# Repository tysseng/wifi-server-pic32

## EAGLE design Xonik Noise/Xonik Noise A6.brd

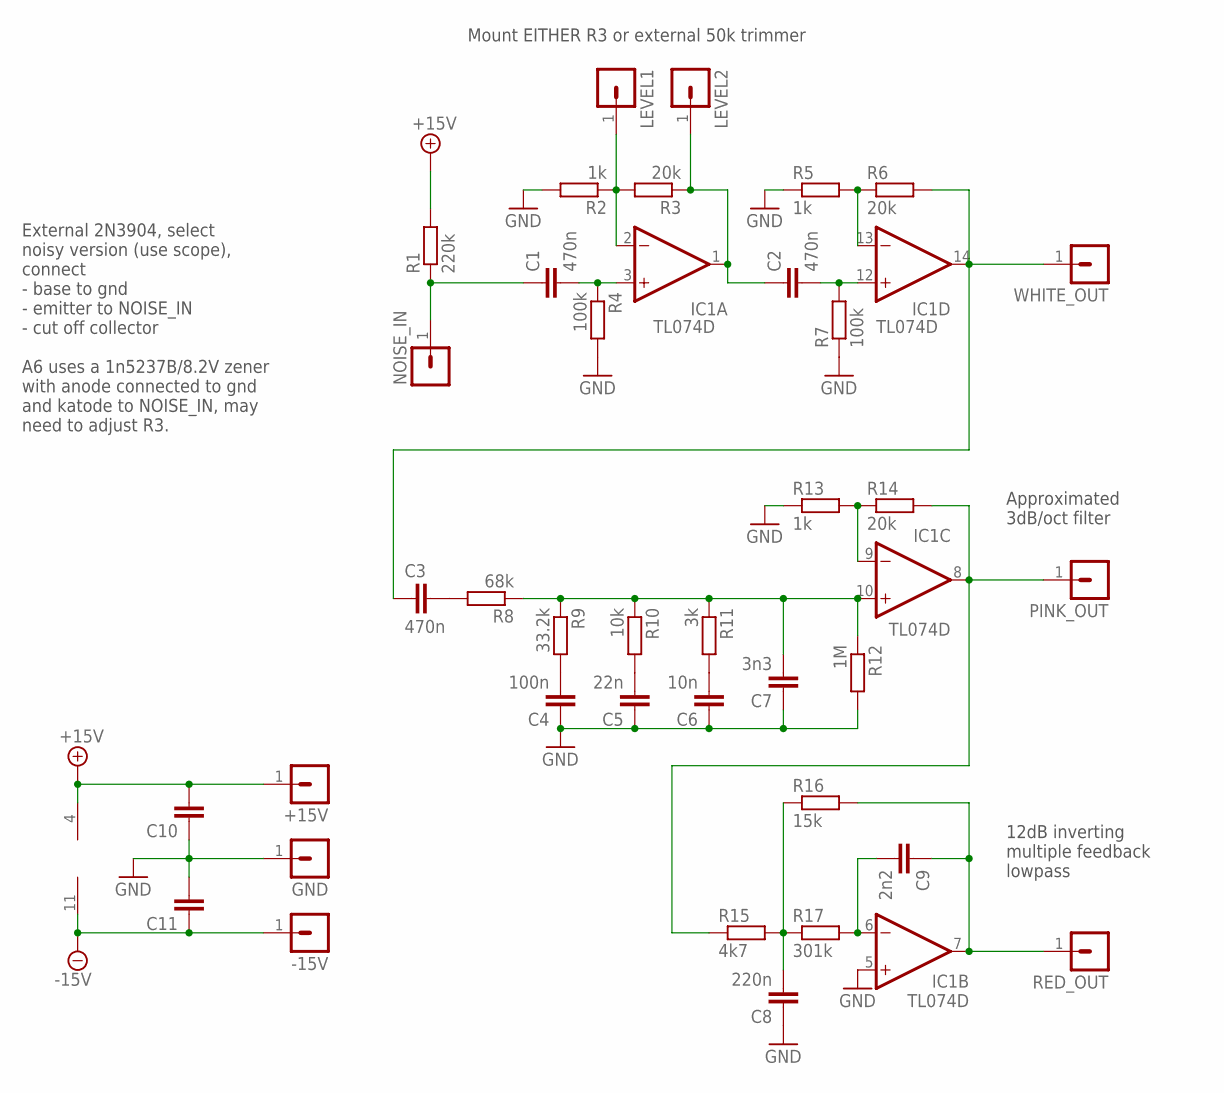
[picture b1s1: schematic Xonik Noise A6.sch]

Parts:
+15V: MA01-1JP; SIP-PIN01-1J
-15V: MA01-1JP; SIP-PIN01-1J
C1, C2, C3: 470n; C0805
C4: 100n; C0805
C5: 22n; C0805
C6: 10n; C0805
C7: 3n3; C0805
C8: 220n; C0805
C9: 2n2; C0805
C10, C11: C-EUC0603; C0603
GND: MA01-1JP; SIP-PIN01-1J
IC1: TL074D; SO14
LEVEL1, LEVEL2: MA01-1JP; SIP-PIN01-1J
NOISE_IN: MA01-1JP; SIP-PIN01-1J
PINK_OUT: MA01-1JP; SIP-PIN01-1J
R1: 220k; R0805
R2, R5, R13: 1k; R0805
R3, R6, R14: 20k; R0805
R4, R7: 100k; R0805
R8: 68k; R0805
R9: 33.2k; R0805
R10: 10k; R0805
R11: 3k; R0805
R12: 1M; R0805
R15: 4k7; R0805
R16: 15k; R0805
R17: 301k; R0805
RED_OUT: MA01-1JP; SIP-PIN01-1J
WHITE_OUT: MA01-1JP; SIP-PIN01-1J

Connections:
+15V: +15V.1, C10.2, IC1.4 (V+), R1.2
-15V: -15V.1, C11.1, IC1.11 (V-)
GND: C4.1, C5.1, C6.1, C7.1, C8.1, C10.1, C11.2, GND.1, IC1.5 (+IN), R2.2, R4.2, R5.1, R7.1, R12.2, R13.1
unnamed: IC1.2 (-IN), LEVEL1.1, R2.1, R3.2
unnamed: IC1.13 (-IN), R5.2, R6.1
unnamed: IC1.9 (-IN), R13.2, R14.1
unnamed: C4.2, R9.2
unnamed: C5.2, R10.2
unnamed: C6.2, R11.2
unnamed: C1.1, NOISE_IN.1, R1.1
unnamed: C1.2, IC1.3 (+IN), R4.1
unnamed: C2.1, IC1.1 (OUT), LEVEL2.1, R3.1
unnamed: C2.2, IC1.12 (+IN), R7.2
unnamed: C3.1, IC1.14 (OUT), R6.2, WHITE_OUT.1
unnamed: C7.2, IC1.10 (+IN), R8.1, R9.1, R10.1, R11.1, R12.1
unnamed: C3.2, R8.2
unnamed: IC1.8 (OUT), PINK_OUT.1, R14.2, R15.1
unnamed: C8.2, R15.2, R16.1, R17.1
unnamed: C9.2, IC1.6 (-IN), R17.2
unnamed: C9.1, IC1.7 (OUT), R16.2, RED_OUT.1

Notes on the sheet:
Mount EITHER R3 or external 50k trimmer
Approximated 3dB/oct filter
12dB inverting multiple feedback lowpass
External 2N3904, select noisy version (use scope), connect - base to gnd - emitter to NOISE_IN - cut off collector A6 uses a 1n5237B/8.2V zener with anode connected to gnd and katode to NOISE_IN, may need to adjust R3.

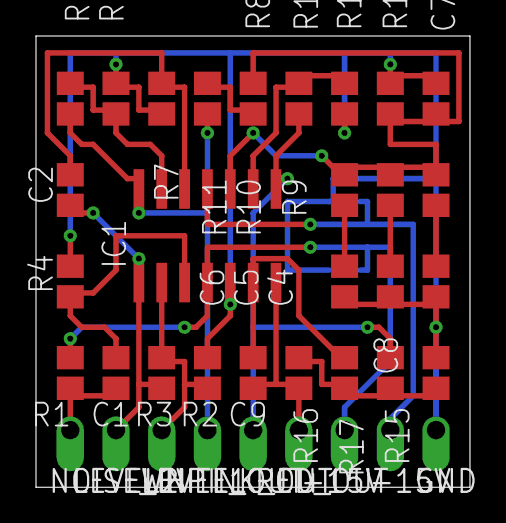
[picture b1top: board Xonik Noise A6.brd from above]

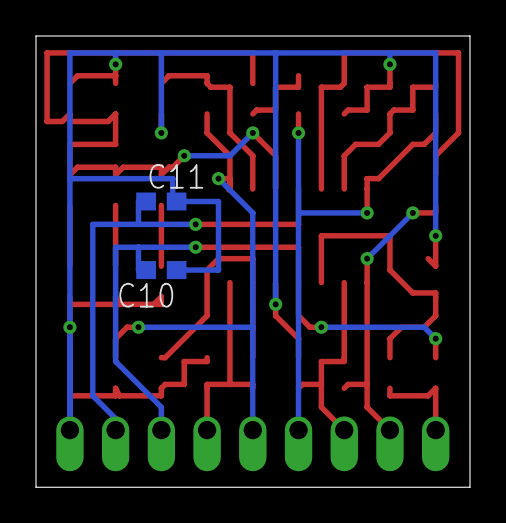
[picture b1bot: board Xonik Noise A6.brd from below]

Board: 2 copper layers, 24.1 x 25.1 mm, 38 parts (2 on the bottom side), 20 nets.

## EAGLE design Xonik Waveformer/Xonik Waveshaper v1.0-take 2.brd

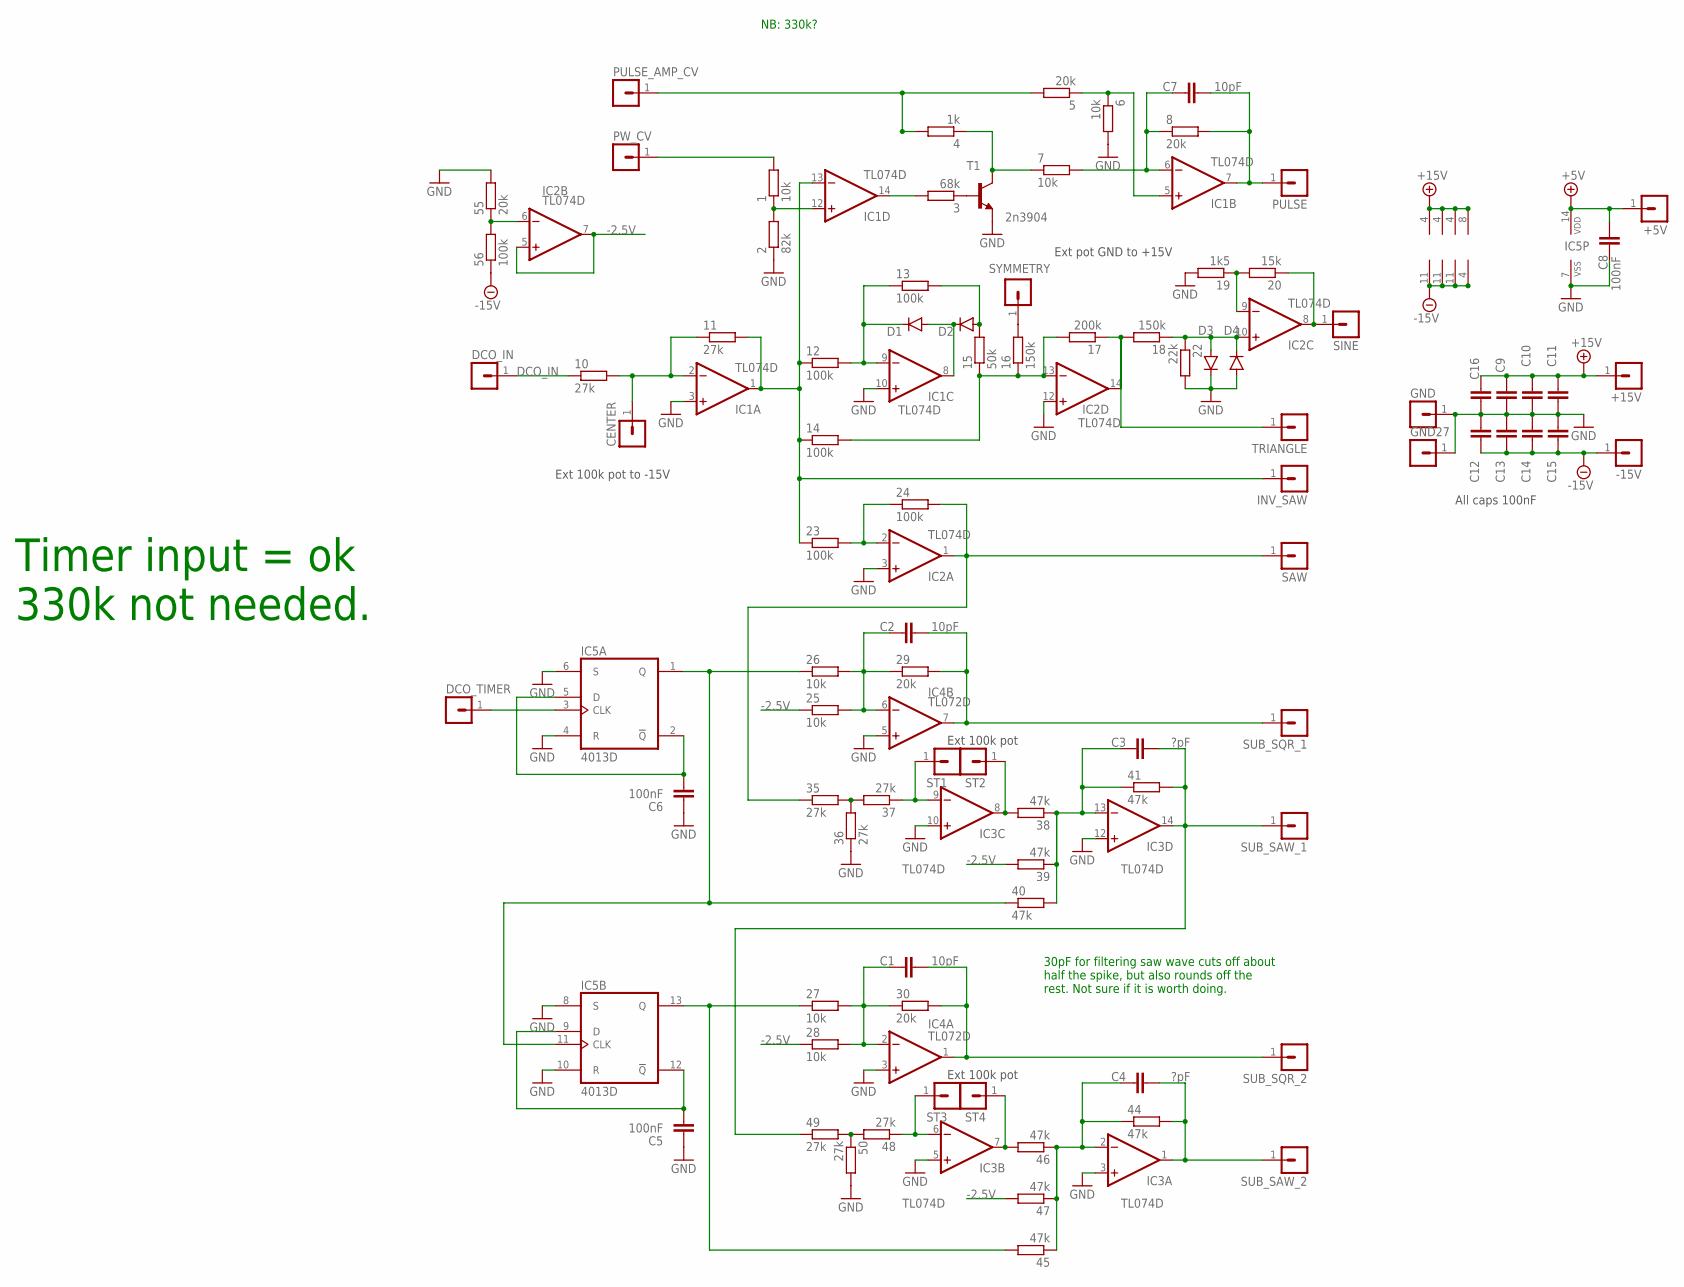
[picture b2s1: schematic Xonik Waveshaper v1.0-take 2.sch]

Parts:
1, 6, 7, 25, 26, 27, 28: 10k; R0805
2: 82k; R0805
3: 68k; R0805
4: 1k; R0805
5, 8, 29, 30, 55: 20k; R0805
10, 11, 35, 36, 37, 48, 49, 50: 27k; R0805
12, 13, 14, 23, 24, 56: 100k; R0805
15: 50k; R0805
16, 18: 150k; R0805
17: 200k; R0805
19: 1k5; R0805
20: 15k; R0805
22: 22k; R0805
38, 39, 40, 41, 44, 45, 46, 47: 47k; R0805
+5V, +15V: MA01-1JP; SIP-PIN01-1J
-15V: MA01-1JP; SIP-PIN01-1J
C1, C2, C7: 10pF; C0805
C3, C4: ?pF; C0805
C5, C6, C8: 100nF; C0805
C9, C10, C11, C12, C13, C14, C15, C16: 100nF; C0603K
CENTER: MA01-1JP; SIP-PIN01-1J
D1, D2, D3, D4: 1N41480805; D0805-J
DCO_IN: MA01-1JP; SIP-PIN01-1J
DCO_TIMER: MA01-1JP; SIP-PIN01-1J
GND, GND27: MA01-1JP; SIP-PIN01-1J
IC1, IC2, IC3: TL074D; SO14
IC4: TL072D; SO08J
IC5: 4013D; SO14J
INV_SAW: MA01-1JP; SIP-PIN01-1J
PULSE: MA01-1JP; SIP-PIN01-1J
PULSE_AMP_CV: MA01-1JP; SIP-PIN01-1J
PW_CV: MA01-1JP; SIP-PIN01-1J
SAW: MA01-1JP; SIP-PIN01-1J
SINE: MA01-1JP; SIP-PIN01-1J
ST1, ST2, ST3, ST4: MA01-1JP; SIP-PIN01-1J
SUB_SAW_1, SUB_SAW_2: MA01-1JP; SIP-PIN01-1J
SUB_SQR_1, SUB_SQR_2: MA01-1JP; SIP-PIN01-1J
SYMMETRY: MA01-1JP; SIP-PIN01-1J
T1: 2n3904; SOT23-BEC
TRIANGLE: MA01-1JP; SIP-PIN01-1J

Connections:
+5V: +5V.1, C8.2, IC5.14 (VDD)
+15V: +15V.1, C9.2, C10.2, C11.2, C16.2, IC1.4 (V+), IC2.4 (V+), IC3.4 (V+), IC4.8 (V+)
-2.5V: 25.1, 28.1, 39.2, 47.2, IC2.5 (+IN), IC2.7 (OUT)
-15V: 56.1, -15V.1, C12.1, C13.1, C14.1, C15.1, IC1.11 (V-), IC2.11 (V-), IC3.11 (V-), IC4.4 (V-)
AMP_CV: 4.2, 5.2, PULSE_AMP_CV.1
DCO_IN: 10.1, DCO_IN.1
GND: 2.1, 6.2, 19.2, 22.2, 36.1, 50.2, 55.2, C5.1, C6.1, C8.1, C9.1, C10.1, C11.1, C12.2, C13.2, C14.2, C15.2, C16.1, D3.C, D4.A, GND.1, GND27.1, IC1.3 (+IN), IC1.10 (+IN), IC2.3 (+IN), IC2.12 (+IN), IC3.3 (+IN), IC3.5 (+IN), IC3.10 (+IN), IC3.12 (+IN), IC4.3 (+IN), IC4.5 (+IN), IC5.4 (R), IC5.6 (S), IC5.7 (VSS), IC5.8 (S), IC5.10 (R), T1.E
unnamed: 1.1, 2.2, IC1.12 (+IN)
unnamed: 3.2, IC1.14 (OUT)
unnamed: 3.1, T1.B
unnamed: 4.1, 7.1, T1.C
unnamed: 5.1, 6.1, IC1.5 (+IN)
unnamed: 7.2, 8.1, C7.1, IC1.6 (-IN)
unnamed: 8.2, C7.2, IC1.7 (OUT), PULSE.1
unnamed: 11.2, 12.1, 14.1, 23.1, IC1.1 (OUT), IC1.13 (-IN), INV_SAW.1
unnamed: 10.2, 11.1, CENTER.1, IC1.2 (-IN)
unnamed: 12.2, 13.1, D1.C, IC1.9 (-IN)
unnamed: D1.A, D2.C, IC1.8 (OUT)
unnamed: 13.2, 15.2, D2.A
unnamed: 14.2, 15.1, 16.1, 17.2, IC2.13 (-IN)
unnamed: 23.2, 24.1, IC2.2 (-IN)
unnamed: 24.2, 35.1, IC2.1 (OUT), SAW.1
unnamed: 29.2, C2.2, IC4.7 (OUT), SUB_SQR_1.1
unnamed: 30.2, C1.2, IC4.1 (OUT), SUB_SQR_2.1
unnamed: 25.2, 26.2, 29.1, C2.1, IC4.6 (-IN)
unnamed: 46.2, IC3.7 (OUT), ST4.1
unnamed: 48.2, 49.2, 50.1
unnamed: 27.2, 28.2, 30.1, C1.1, IC4.2 (-IN)
unnamed: 35.2, 36.2, 37.2
unnamed: 37.1, IC3.9 (-IN), ST1.1
unnamed: 38.1, 39.1, 40.2, 41.1, C3.1, IC3.13 (-IN)
unnamed: 41.2, 49.1, C3.2, IC3.14 (OUT), SUB_SAW_1.1
unnamed: 48.1, IC3.6 (-IN), ST3.1
unnamed: 44.1, 45.1, 46.1, 47.1, C4.1, IC3.2 (-IN)
unnamed: 44.2, C4.2, IC3.1 (OUT), SUB_SAW_2.1
unnamed: C6.2, IC5.2 (!Q), IC5.5 (D)
unnamed: 26.1, 40.1, IC5.1 (Q), IC5.11 (CLK)
unnamed: 55.1, 56.2, IC2.6 (-IN)
unnamed: C5.2, IC5.9 (D), IC5.12 (!Q)
unnamed: 27.1, 45.2, IC5.13 (Q)
unnamed: 19.1, 20.2, IC2.9 (-IN)
unnamed: 16.2, SYMMETRY.1
unnamed: 17.1, 18.2, IC2.14 (OUT), TRIANGLE.1
unnamed: 18.1, 22.1, D3.A, D4.C, IC2.10 (+IN)
unnamed: 20.1, IC2.8 (OUT), SINE.1
unnamed: 38.2, IC3.8 (OUT), ST2.1
PW_CV: 1.2, PW_CV.1
SQR: DCO_TIMER.1, IC5.3 (CLK)

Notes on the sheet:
NB: 330k?
All caps 100nF
Ext 100k pot to -15V
Ext pot GND to +15V
Ext 100k pot
Timer input = ok 330k not needed.
30pF for filtering saw wave cuts off about half the spike, but also rounds off the rest. Not sure if it is worth doing.

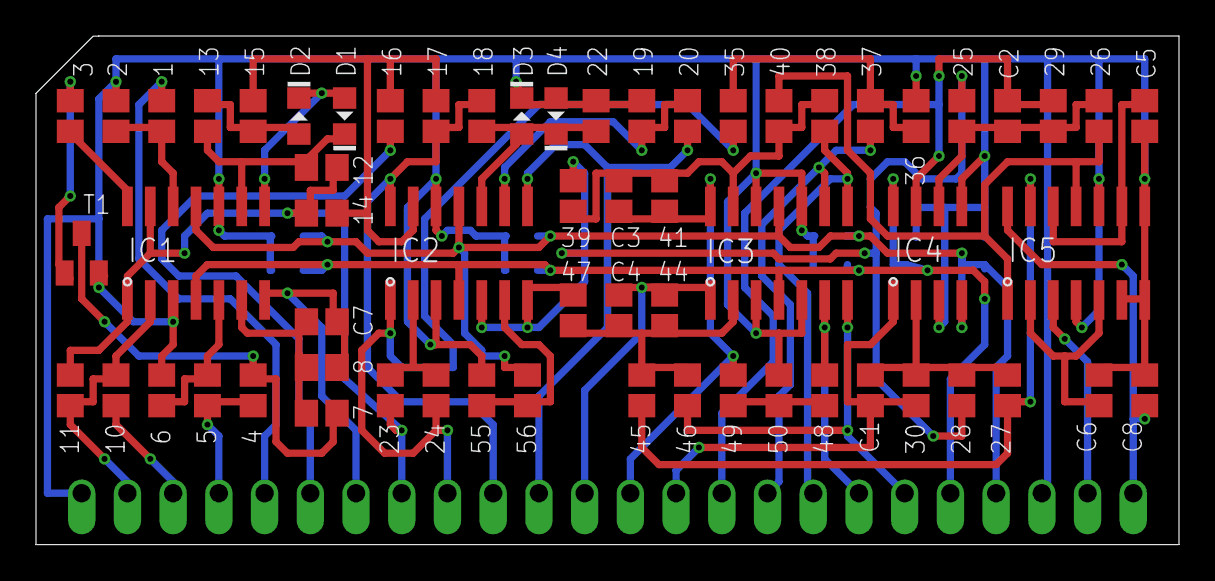
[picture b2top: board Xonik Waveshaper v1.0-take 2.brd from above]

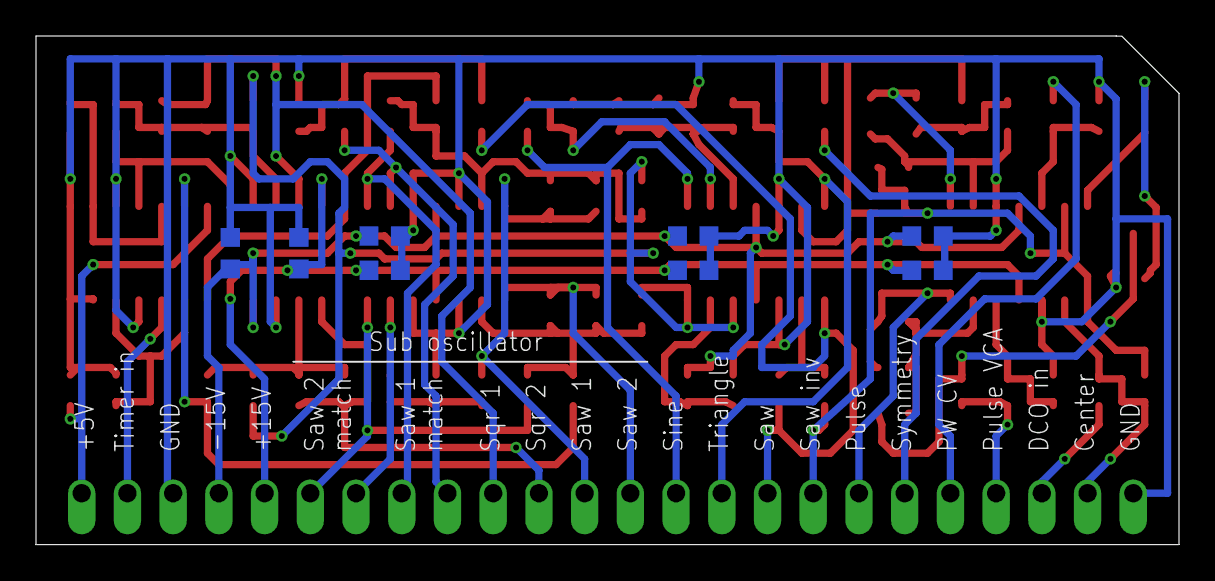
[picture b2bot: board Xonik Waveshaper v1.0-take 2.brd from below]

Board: 2 copper layers, 63.5 x 28.3 mm, 94 parts (8 on the bottom side), 48 nets.

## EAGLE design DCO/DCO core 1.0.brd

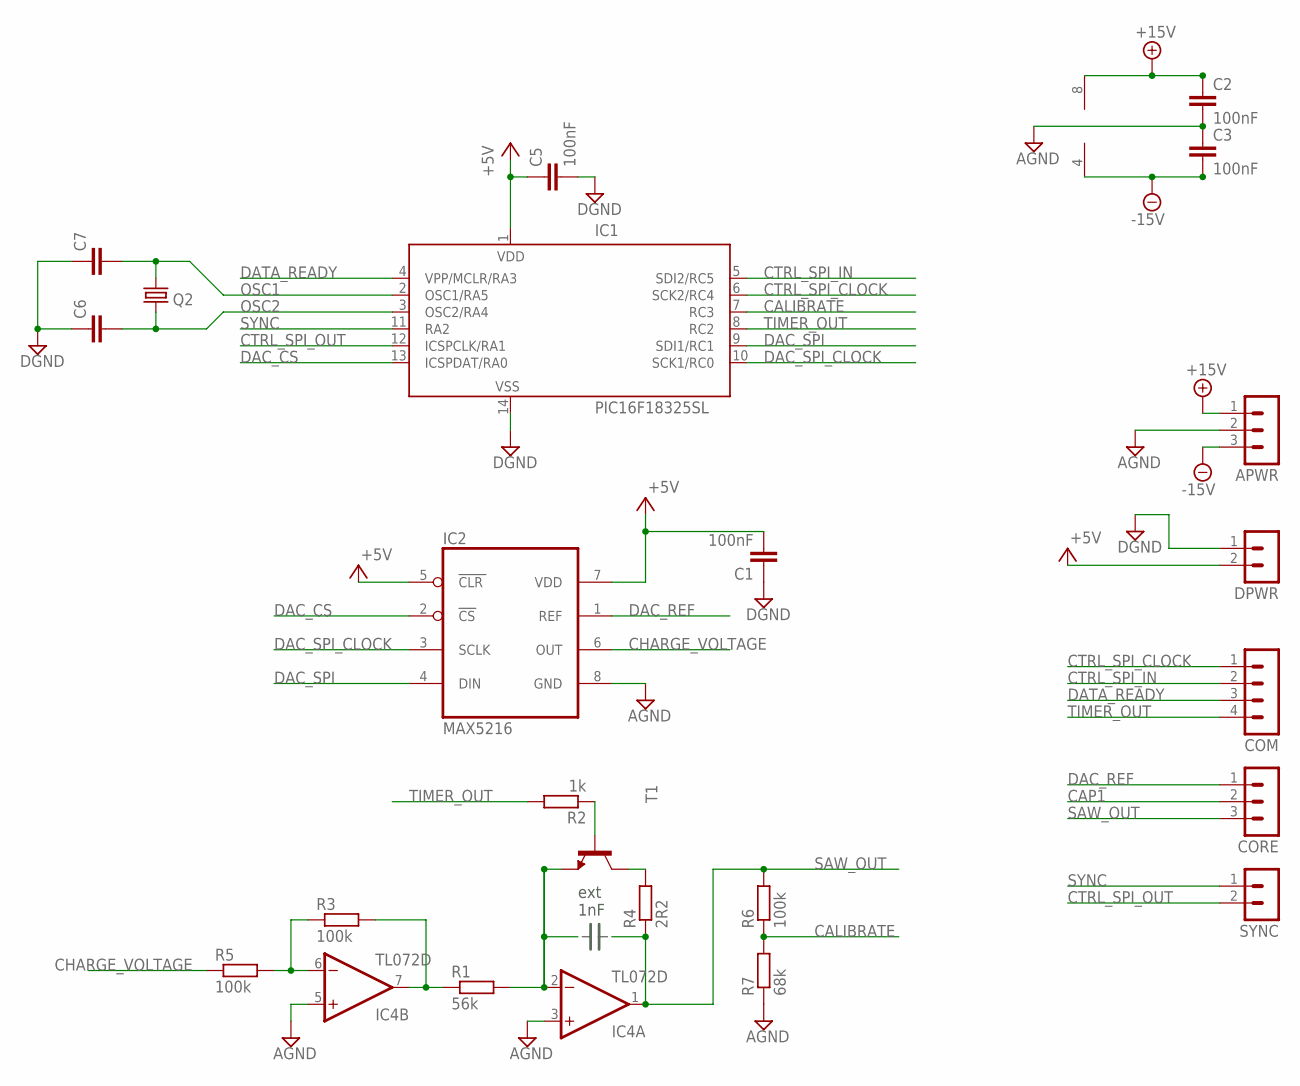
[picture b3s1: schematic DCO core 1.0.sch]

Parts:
APWR: MA03-1JP; SIP-PIN03-1J
C1, C2, C3, C5: 100nF; C0805
C6, C7: C-EUC0805; C0805
COM: MA04-1JP; SIP-PIN04-1J
CORE: MA03-1JP; SIP-PIN03-1J
DPWR: MA02-1JP; SIP-PIN02-1J
IC1: PIC16F18325SL; SO14J
IC2: MAX5216; UMAX8J
IC4: TL072D; SO08J
Q2: CRYSTALHC49S; HC49/S
R1: 56k; R0805
R2: 1k; R0805
R3, R5, R6: 100k; R0805
R4: 2R2; R0805
R7: 68k; R0805
SYNC: MA02-1JP; SIP-PIN02-1J
T1: MMBT3904LT1-NPN-SOT23-BEC; SOT23-BEC

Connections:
+5V: C1.2, C5.1, DPWR.2, IC1.1 (VDD), IC2.5 (CLR), IC2.7 (VDD)
+15V: APWR.1, C2.1, IC4.8 (V+)
-15V: APWR.3, C3.2, IC4.4 (V-)
AGND: APWR.2, C2.2, C3.1, IC2.8 (GND), IC4.3 (+IN), IC4.5 (+IN), R7.1
CALIBRATE: IC1.7 (RC3), R6.1, R7.2
CAP1: CORE.2, IC4.2 (-IN), R1.2, T1.E
CHARGE_VOLTAGE: IC2.6 (OUT), R5.1
CTRL_SPI_CLOCK: COM.1, IC1.6 (SCK2/RC4)
CTRL_SPI_IN: COM.2, IC1.5 (SDI2/RC5)
CTRL_SPI_OUT: IC1.12 (ICSPCLK/RA1), SYNC.2
DAC_CS: IC1.13 (ICSPDAT/RA0), IC2.2 (CS)
DAC_REF: CORE.1, IC2.1 (REF)
DAC_SPI: IC1.9 (SDI1/RC1), IC2.4 (DIN)
DAC_SPI_CLOCK: IC1.10 (SCK1/RC0), IC2.3 (SCLK)
DATA_READY: COM.3, IC1.4 (VPP/MCLR/RA3)
DGND: C1.1, C5.2, C6.1, C7.1, DPWR.1, IC1.14 (VSS)
unnamed: R4.2, T1.C
unnamed: R2.1, T1.B
unnamed: IC4.6 (-IN), R3.1, R5.2
unnamed: IC4.7 (OUT), R1.1, R3.2
OSC1: C7.2, IC1.2 (OSC1/RA5), Q2.2
OSC2: C6.2, IC1.3 (OSC2/RA4), Q2.1
SAW_OUT: CORE.3, IC4.1 (OUT), R4.1, R6.2
SYNC: IC1.11 (RA2), SYNC.1
TIMER_OUT: COM.4, IC1.8 (RC2), R2.2

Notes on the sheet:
ext 1nF

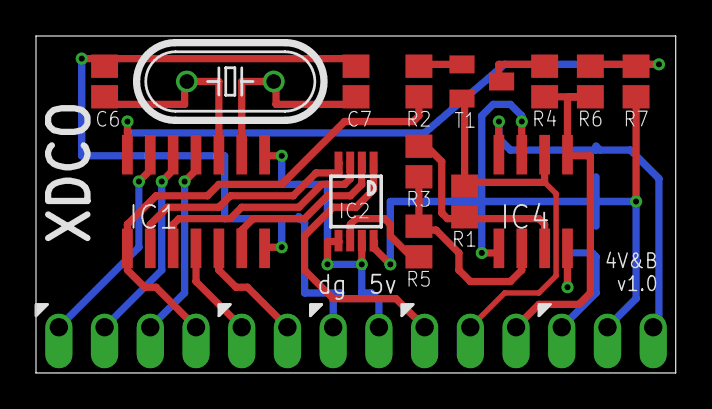
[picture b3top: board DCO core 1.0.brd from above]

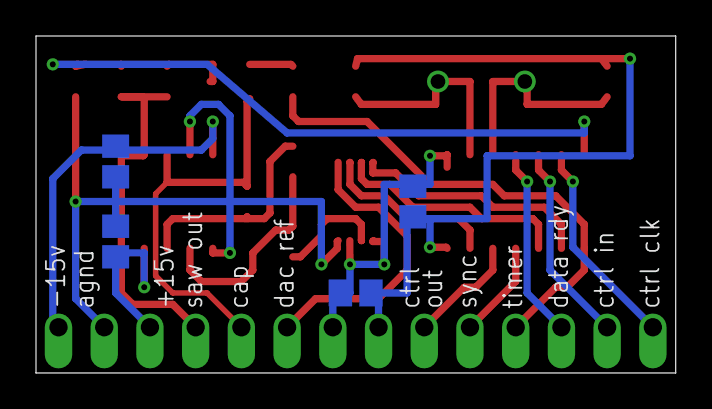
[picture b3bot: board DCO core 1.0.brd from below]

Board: 2 copper layers, 35.5 x 18.7 mm, 23 parts (4 on the bottom side), 25 nets.

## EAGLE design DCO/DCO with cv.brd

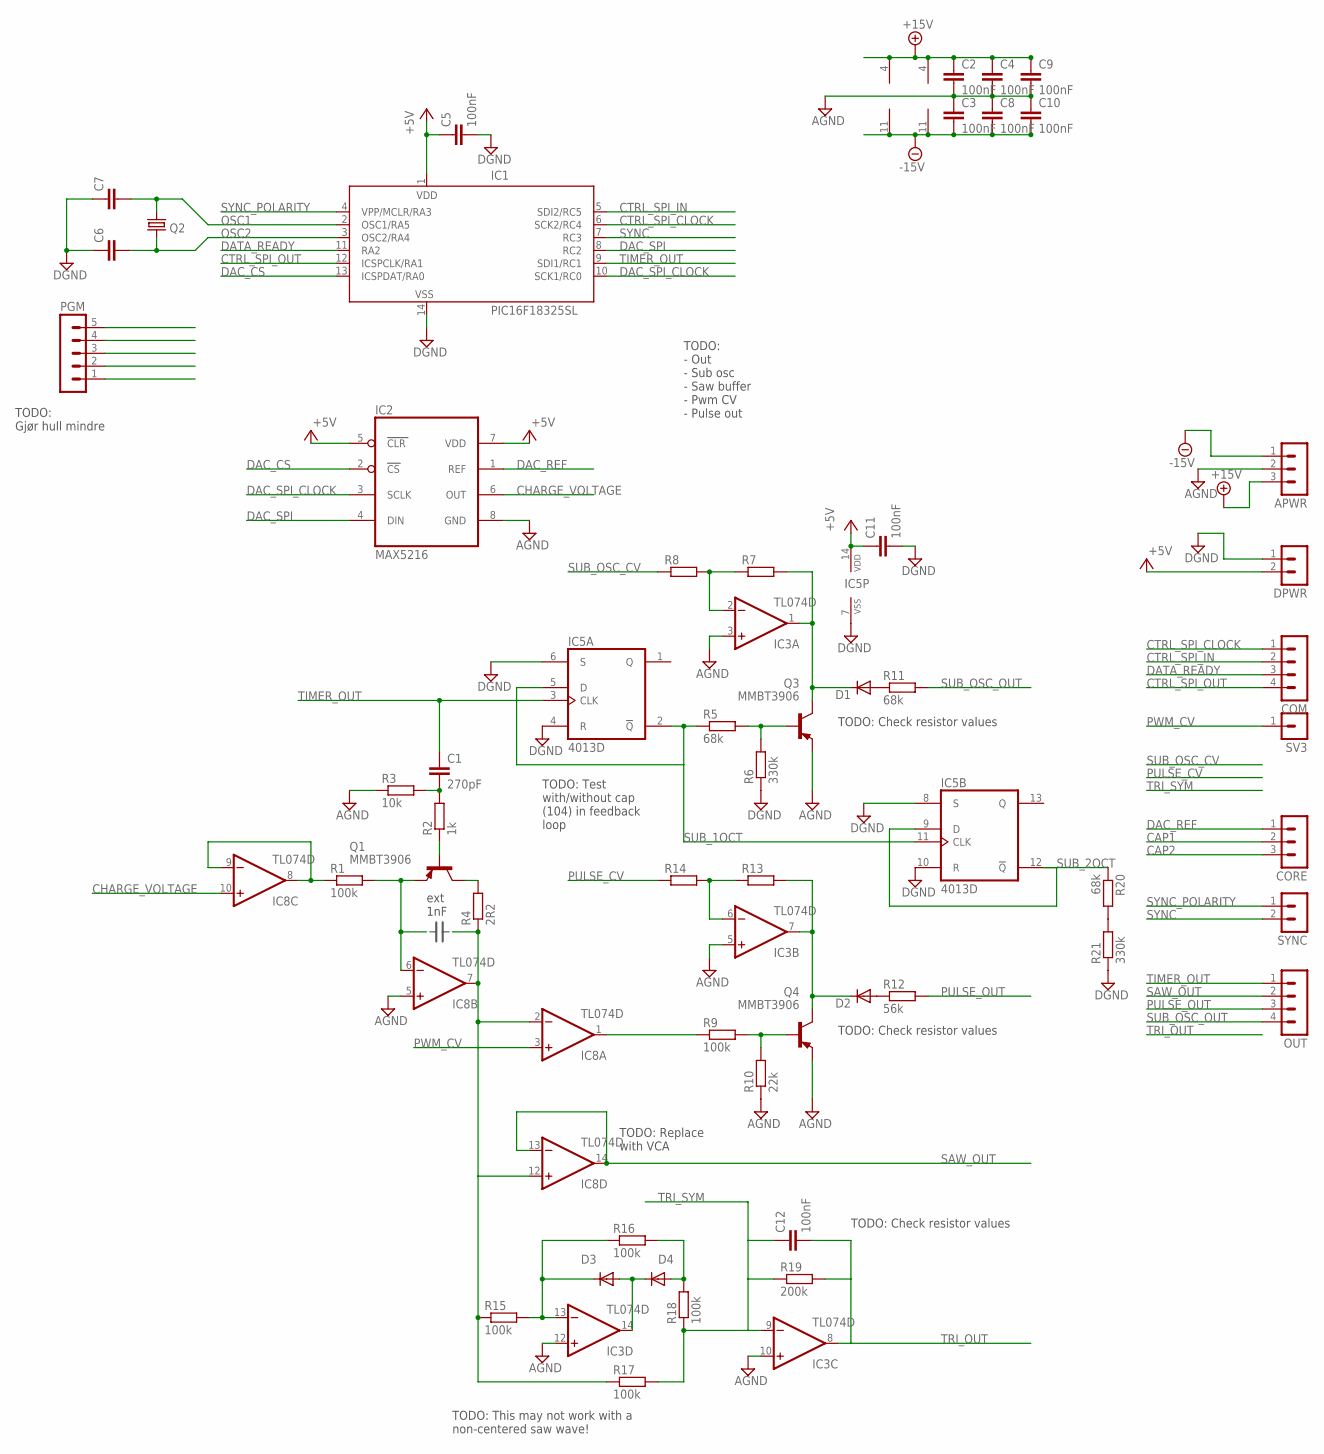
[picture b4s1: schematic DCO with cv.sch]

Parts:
APWR: MA03-1J
C1: 270pF; C0805
C2, C3, C4, C5, C8, C9, C10, C11, C12: 100nF; C0805
C6, C7: C-EUC0805; C0805
COM: MA04-1J
CORE: MA03-1J
D1, D2, D3, D4: DIODE-SOD80C; SOD80C
DPWR: MA02-1J
IC1: PIC16F18325SL; SO14J
IC2: MAX5216; UMAX8J
IC3, IC8: TL074D; SO14
IC5: 4013D; SO14J
OUT: MA04-1J
PGM: MA05-1J
Q1, Q3, Q4: MMBT3906; SOT23-BEC
Q2: CRYSTALHC49S; HC49/S
R1, R9, R15, R16, R17, R18: 100k; R0805
R2: 1k; R0805
R3: 10k; R0805
R4: 2R2; R0805
R5, R11, R20: 68k; R0805
R6, R21: 330k; R0805
R7, R8, R13, R14: R-EU_R0805; R0805
R10: 22k; R0805
R12: 56k; R0805
R19: 200k; R0805
SV3: MA01-1J
SYNC: MA02-1J

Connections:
+5V: C5.1, C11.1, DPWR.2, IC1.1 (VDD), IC2.5 (CLR), IC2.7 (VDD), IC5.14 (VDD)
+15V: APWR.3, C2.1, IC3.4 (V+), IC8.4 (V+)
+15V1: C4.1
+15V2: C9.1
-15V: APWR.1, C3.2, IC3.11 (V-), IC8.11 (V-)
-15V1: C8.2
-15V2: C10.2
AGND: APWR.2, C2.2, C3.1, C4.2, C8.1, C9.2, C10.1, IC2.8 (GND), IC3.3 (+IN), IC3.5 (+IN), IC3.10 (+IN), IC3.12 (+IN), IC8.5 (+IN), Q3.E, Q4.E, R3.1, R10.1
CAP1: CORE.2, IC8.6 (-IN), Q1.E, R1.2
CAP2: CORE.3, IC8.2 (-IN), IC8.7 (OUT), IC8.12 (+IN), R4.1, R15.1, R17.1
CHARGE_VOLTAGE: IC2.6 (OUT), IC8.10 (+IN)
CTRL_SPI_CLOCK: COM.1, IC1.6 (SCK2/RC4)
CTRL_SPI_IN: COM.2, IC1.5 (SDI2/RC5)
CTRL_SPI_OUT: COM.4, IC1.12 (ICSPCLK/RA1)
DAC_CS: IC1.13 (ICSPDAT/RA0), IC2.2 (CS)
DAC_REF: CORE.1, IC2.1 (REF)
DAC_SPI: IC1.8 (RC2), IC2.4 (DIN)
DAC_SPI_CLOCK: IC1.10 (SCK1/RC0), IC2.3 (SCLK)
DATA_READY: COM.3, IC1.11 (RA2)
DGND: C5.2, C6.1, C7.1, C11.2, DPWR.1, IC1.14 (VSS), IC5.4 (R), IC5.6 (S), IC5.7 (VSS), IC5.8 (S), IC5.10 (R), R6.1, R21.1
unnamed: R20.2, R21.2
unnamed: Q1.B, R2.1
unnamed: Q1.C, R4.2
unnamed: C1.2, R2.2, R3.2
unnamed: IC8.8 (OUT), IC8.9 (-IN), R1.1
unnamed: Q3.B, R5.2, R6.2
unnamed: D1.C, IC3.1 (OUT), Q3.C, R7.2
unnamed: IC8.1 (OUT), R9.1
unnamed: Q4.B, R9.2, R10.2
unnamed: IC3.2 (-IN), R7.1, R8.2
unnamed: D2.C, IC3.7 (OUT), Q4.C, R13.2
unnamed: D1.A, R11.1
unnamed: D2.A, R12.1
unnamed: D3.C, IC3.13 (-IN), R15.2, R16.1
unnamed: IC3.6 (-IN), R13.1, R14.2
unnamed: D3.A, D4.C, IC3.14 (OUT)
unnamed: D4.A, R16.2, R18.2
OSC1: C7.2, IC1.2 (OSC1/RA5), Q2.2
OSC2: C6.2, IC1.3 (OSC2/RA4), Q2.1
PULSE_CV: R14.1
PULSE_OUT: OUT.3, R12.2
PWM_CV: IC8.3 (+IN), SV3.1
SAW_OUT: IC8.13 (-IN), IC8.14 (OUT), OUT.2
SUB_1OCT: IC5.2 (!Q), IC5.5 (D), IC5.11 (CLK), R5.1
SUB_2OCT: IC5.9 (D), IC5.12 (!Q), R20.1
SUB_OSC_CV: R8.1
SUB_OSC_OUT: OUT.4, R11.2
SYNC: IC1.7 (RC3), SYNC.2
SYNC_POLARITY: IC1.4 (VPP/MCLR/RA3), SYNC.1
TIMER_OUT: C1.1, IC1.9 (SDI1/RC1), IC5.3 (CLK), OUT.1
TRI_OUT: C12.2, IC3.8 (OUT), R19.2
TRI_SYM: C12.1, IC3.9 (-IN), R17.2, R18.1, R19.1

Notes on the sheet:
ext 1nF
TODO: - Out - Sub osc - Saw buffer - Pwm CV - Pulse out
TODO: Gjør hull mindre
TODO: Test with/without cap (104) in feedback loop
TODO: Replace with VCA
TODO: Check resistor values
TODO: This may not work with a non-centered saw wave!

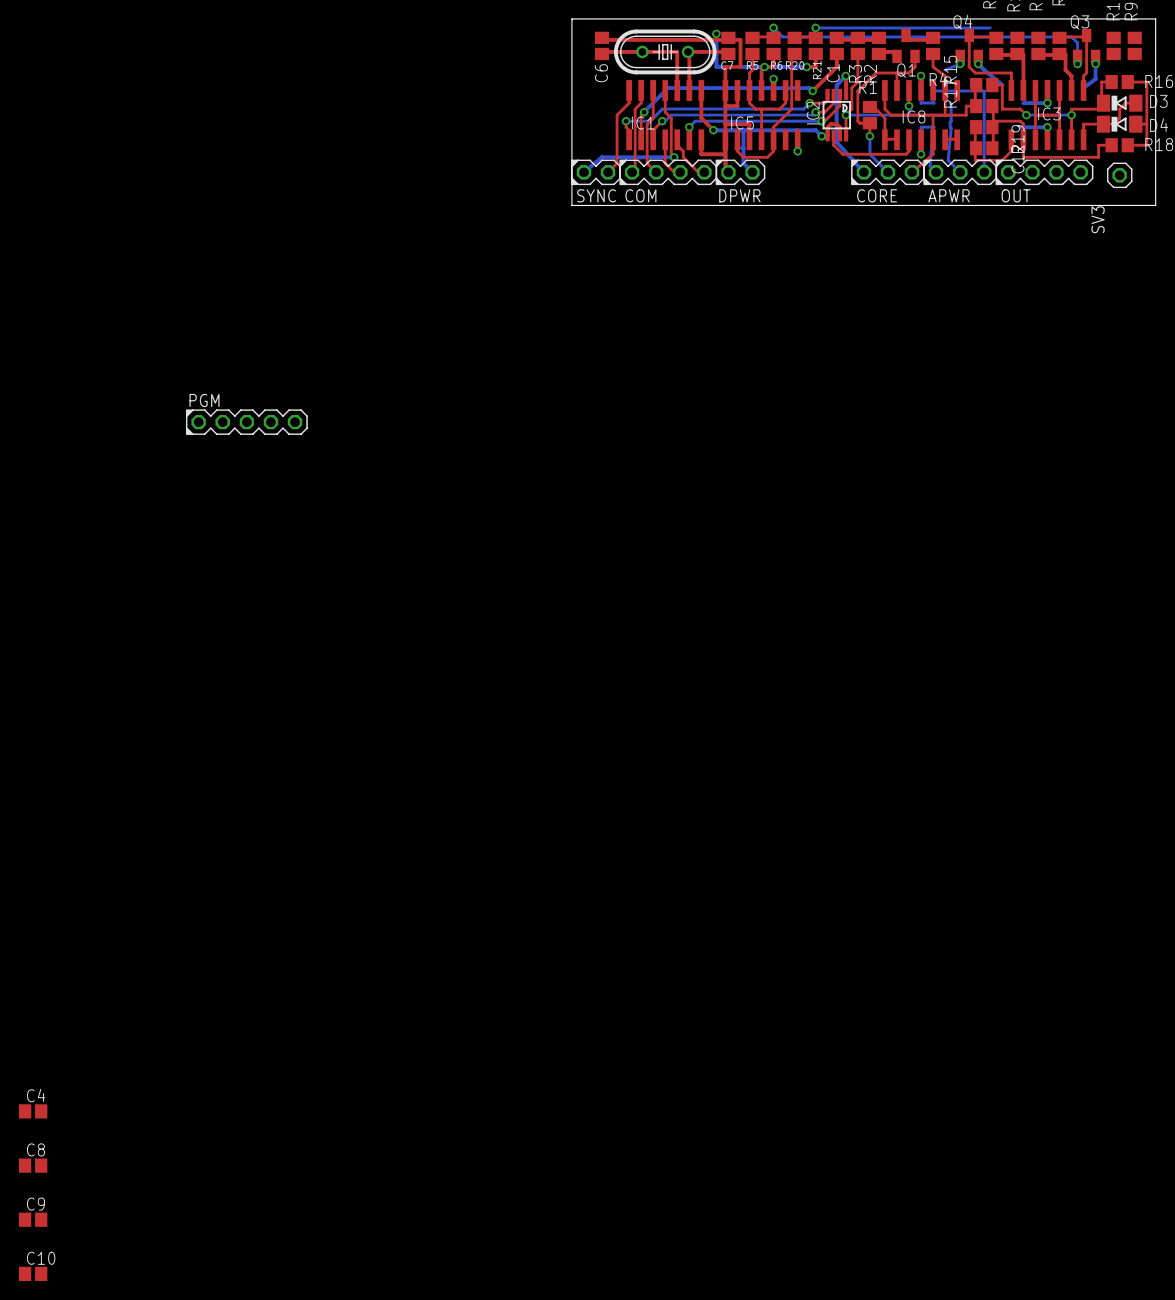
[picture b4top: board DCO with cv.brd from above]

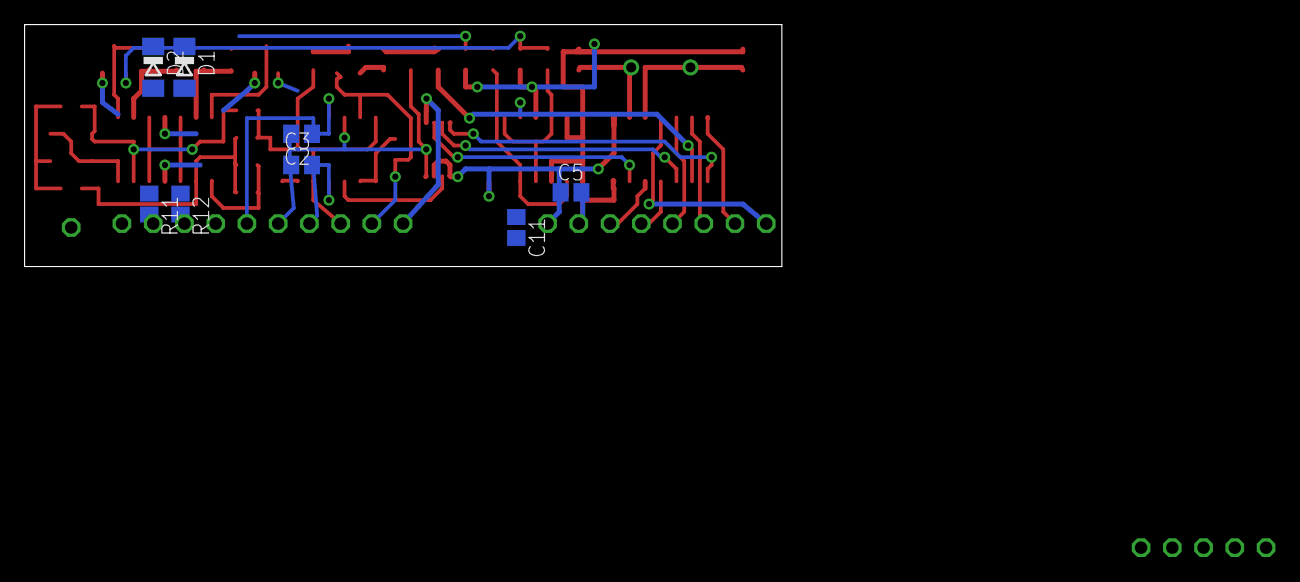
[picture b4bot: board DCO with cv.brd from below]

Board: 2 copper layers, 61.6 x 19.7 mm, 54 parts (8 on the bottom side), 46 nets.

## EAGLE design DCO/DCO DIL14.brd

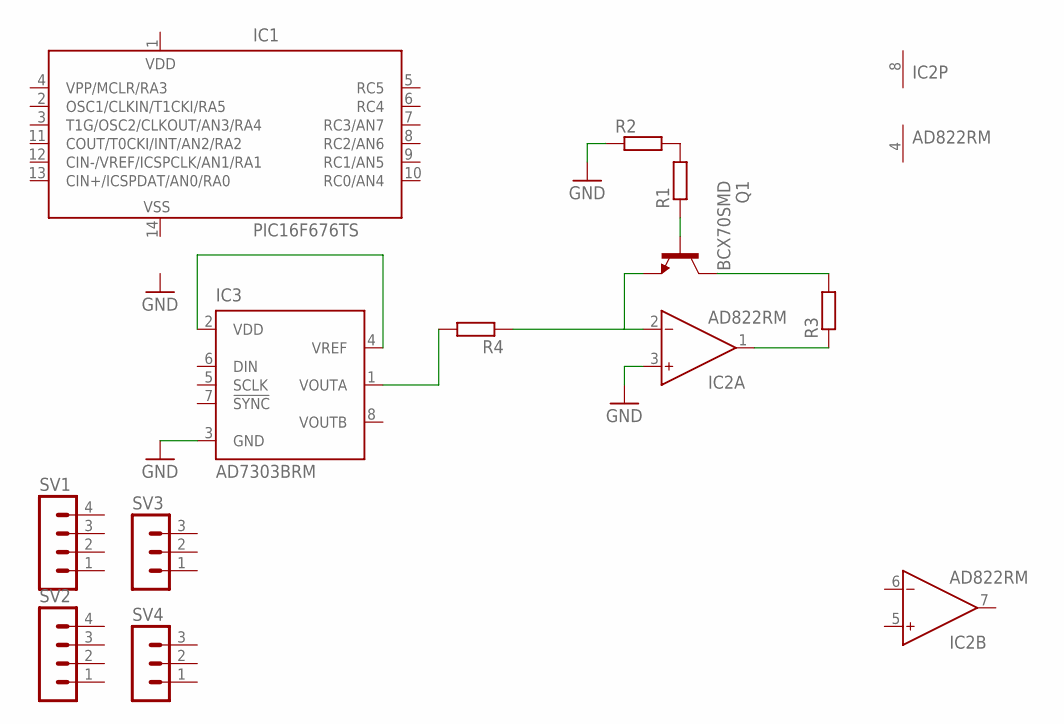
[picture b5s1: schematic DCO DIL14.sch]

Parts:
IC1: PIC16F676TS; TSSOP14
IC2: AD822RM; MSOP08
IC3: AD7303BRM; MSOP08
Q1: BCX70SMD; SOT23
R1, R2, R3, R4: R-EU_R0603; R0603
SV1, SV2: MA04-1J
SV3, SV4: MA03-1J

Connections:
GND: IC2.3 (IN+), IC3.3 (GND), R2.1
unnamed: R1.2, R2.2
unnamed: IC2.1 (OUT), R3.1
unnamed: IC2.2 (IN-), Q1.2 (E), R4.1
unnamed: IC3.1 (VOUTA), R4.2
unnamed: IC3.2 (VDD), IC3.4 (VREF)
unnamed: Q1.3 (C), R3.2
unnamed: Q1.1 (B), R1.1
V+: IC2.8 (V+)
V-: IC2.4 (V-)
VDD: IC1.1 (VDD)
VSS: IC1.14 (VSS)

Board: 2 copper layers, 12 parts (3 on the bottom side), 8 nets, no tracks yet.

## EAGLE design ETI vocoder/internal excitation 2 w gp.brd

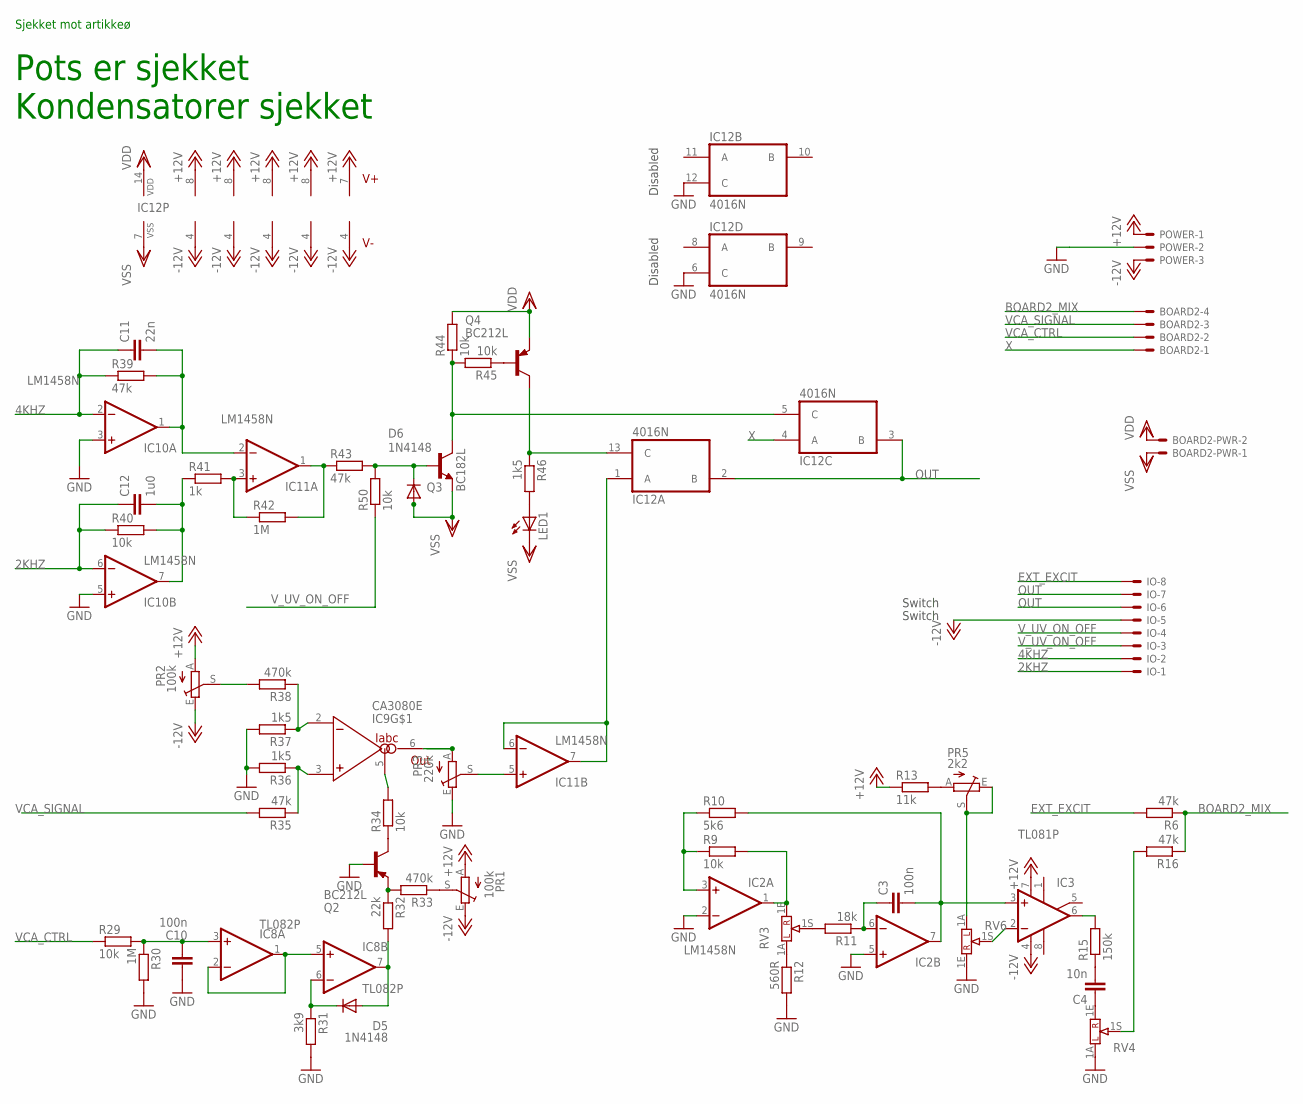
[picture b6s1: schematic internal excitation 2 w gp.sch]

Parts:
BOARD2: 22-23-2041
BOARD2-PWR: 22-23-2021
C3, C10: 100n; C075-032X103
C4: 10n; C025-025X050
C11: 22n; C050-025X075
C12: 1u0; C050-025X075
D5, D6: 1N4148; DO35-5J
IC2, IC10, IC11: LM1458N; DIL08
IC3: TL081P; DIL08
IC8: TL082P; DIL08
IC9: CA3080E; DIL08
IC12: 4016N; DIL14
IO: 22-23-2081
LED1: LED3MM
POWER: KK-156-3
PR1, PR2: 100k; CA9V
PR3: 220k; CA9V
PR5: 2k2; CA9V
Q2, Q4: BC212L; TO92-CBE
Q3: BC182L; TO92-ECB
R6: 47k; 0207/10
R9, R29, R34, R40, R44, R45, R50: 10k; 0207/7
R10: 5k6; 0207/7
R11: 18k; 0207/7
R12: 560R; 0207/7
R13: 11k; 0207/7
R15: 150k; 0207/7
R16, R35, R39, R43: 47k; 0207/7
R30, R42: 1M; 0207/7
R31: 3k9; 0207/7
R32: 22k; 0207/7
R33, R38: 470k; 0207/7
R36, R37, R46: 1k5; 0207/7
R41: 1k; 0207/7
RV3, RV4: 10k log; POT16_W_BRACKET
RV6: 10k; POT16_W_BRACKET

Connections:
2KHZ: C12.1, IC10.6 (-IN), IO.1, R40.1
4KHZ: C11.1, IC10.2 (-IN), IO.2, R39.1
+12V: IC2.8 (V+), IC3.7 (V+), IC8.8 (V+), IC9.7 (V+), IC10.8 (V+), IC11.8 (V+), POWER.1, PR1.A, PR2.A, R13.1
-12V: IC2.4 (V-), IC3.4 (V-), IC8.4 (V-), IC9.4 (V-), IC10.4 (V-), IC11.4 (V-), IO.5, POWER.3, PR1.E, PR2.E
BOARD2_MIX: BOARD2.4, R6.1, R16.1
EXT_EXCIT: IO.8, R6.2
GND: C10.1, IC2.2 (-IN), IC2.5 (+IN), IC10.3 (+IN), IC10.5 (+IN), IC12.6 (C), IC12.12 (C), POWER.2, PR3.E, Q2.B, R12.2, R30.2, R31.2, R36.2, R37.2, RV4.1A, RV6.1E
unnamed: IC2.3 (+IN), R9.1, R10.1
unnamed: IC2.1 (OUT), R9.2, RV3.1E
unnamed: R11.2, RV3.1S
unnamed: C3.1, IC2.6 (-IN), R11.1
unnamed: R12.1, RV3.1A
unnamed: C3.2, IC2.7 (OUT), IC3.3 (+IN), R10.2
unnamed: IC3.2 (-IN), RV6.1S
unnamed: PR5.A, R13.2
unnamed: PR5.E, PR5.S, RV6.1A
unnamed: IC3.6 (OUT), R15.2
unnamed: C4.2, R15.1
unnamed: C4.1, RV4.1E
unnamed: R16.2, RV4.1S
unnamed: IC11.3 (+IN), R41.2, R42.1
unnamed: C11.2, IC10.1 (OUT), IC11.2 (-IN), R39.2
unnamed: IC11.1 (OUT), R42.2, R43.1
unnamed: C12.2, IC10.7 (OUT), R40.2, R41.1
unnamed: LED1.A, R46.2
unnamed: IC12.5 (C), Q3.C, R44.1, R45.2
unnamed: Q4.B, R45.1
unnamed: D6.C, Q3.B, R43.2, R50.2
unnamed: IC9.6 (OUT), PR3.A
unnamed: IC12.13 (C), Q4.C, R46.1
unnamed: Q2.C, R34.1
unnamed: IC9.3 (+IN), R35.1, R36.1
unnamed: IC9.2 (-IN), R37.1, R38.1
unnamed: PR2.S, R38.2
unnamed: IC9.5 (IABC), R34.2
unnamed: Q2.E, R32.1, R33.2
unnamed: PR1.S, R33.1
unnamed: IC11.5 (+IN), PR3.S
unnamed: IC11.6 (-IN), IC11.7 (OUT), IC12.1 (A)
unnamed: D5.A, IC8.7 (OUT), R32.2
unnamed: IC8.1 (OUT), IC8.2 (-IN), IC8.5 (+IN)
unnamed: D5.C, IC8.6 (-IN), R31.1
unnamed: C10.2, IC8.3 (+IN), R29.2, R30.1
OUT: IC12.2 (B), IC12.3 (B), IO.6, IO.7
VCA_CTRL: BOARD2.2, R29.1
VCA_SIGNAL: BOARD2.3, R35.2
VDD: BOARD2-PWR.2, IC12.14 (VDD), Q4.E, R44.2
VSS: BOARD2-PWR.1, D6.A, IC12.7 (VSS), LED1.K (C), Q3.E
V_UV_ON_OFF: IO.3, IO.4, R50.1
X: BOARD2.1, IC12.4 (A)

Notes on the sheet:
Switch
Disabled
Pots er sjekket
Kondensatorer sjekket
Sjekket mot artikkeø

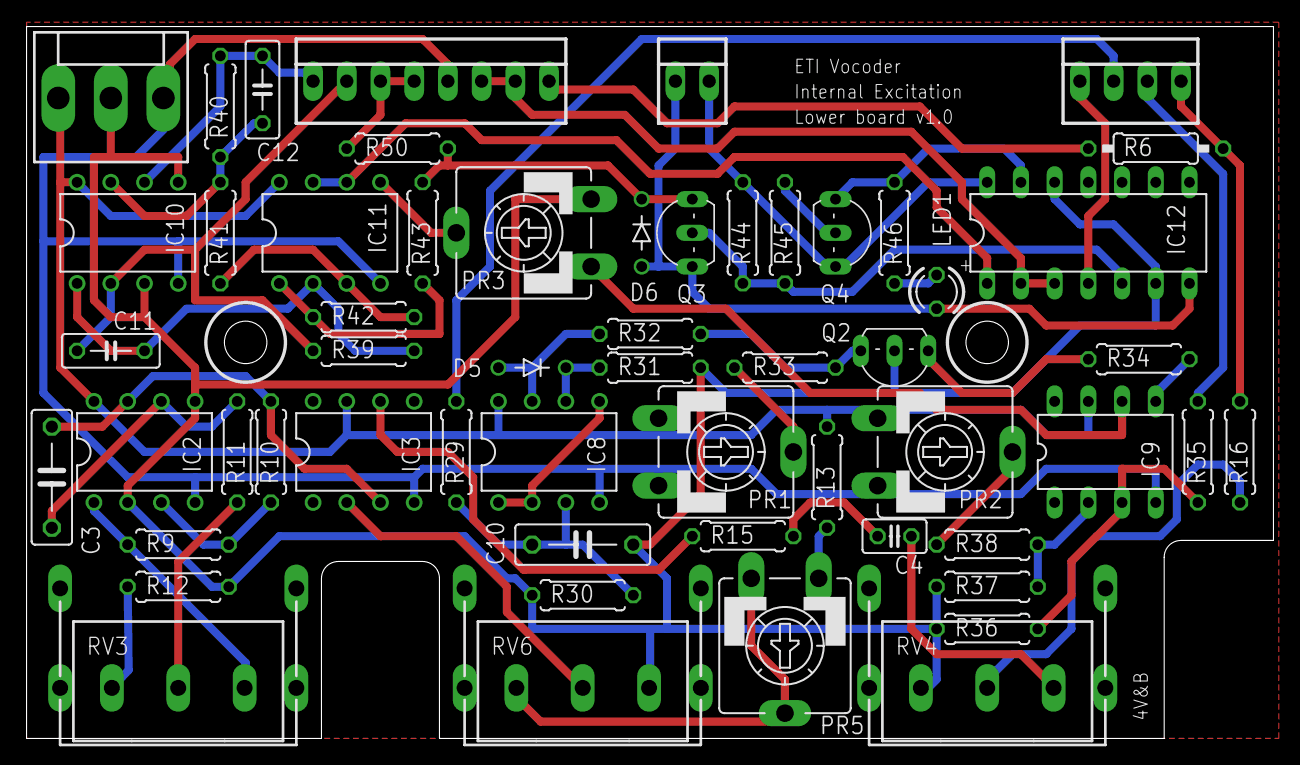
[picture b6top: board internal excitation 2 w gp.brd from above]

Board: 2 copper layers, 94.0 x 53.6 mm, 56 parts (0 on the bottom side), 50 nets.
